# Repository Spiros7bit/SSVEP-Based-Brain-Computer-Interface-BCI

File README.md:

# SSVEP-Based Brain-Computer Interface

## Overview

This project implements a real-time Steady-State Visually Evoked Potential (SSVEP) Brain-Computer Interface (BCI) using an ESP32 microcontroller and a custom PCB for analog interface. It was developed as part of a thesis and demonstrates how EEG signals can be processed and classified in real time on embedded hardware.

The system detects brain responses to visual stimuli at specific frequencies and converts them into control decisions.

---

## System Architecture

The signal processing pipeline consists of the following stages:

1. **Analog Interface**
   
   * Instrumentation Amplifier
   * Low Pass Filter, Sallen Key, 2 order
   * AC amplifier
   * Notch 50 Hz filter
   * Final AC Amplifier
   * Right Leg Driver circuit
     
3. **Signal Acquisition**

   * ADC sampling at 1 kHz
   * Hardware timer interrupt for precise timing

4. **Preprocessing**

   * DC offset removal (IIR high-pass filter)
   * FIR band-pass filtering

5. **Feature Extraction**

   * Goertzel algorithm for frequency detection
   * Target frequencies: 10 Hz, 12 Hz, 20 Hz, 24 Hz

6. **Decision Making**

   * Argmax power comparison
   * Median Absolute Deviation (MAD)-based classifier

7. **Output**

   * Real-time signal visualization via Serial Plotter
   * Classification results (Argmax & MAD)

---

## Features

* Analog interface and Acquition System
* Real-time processing on ESP32
* 1 kHz sampling using hardware timer interrupts
* Efficient fixed-point DSP implementation
* FIR filtering with circular buffer
* Sliding window Goertzel analysis (with overlap)
* Robust classification using MAD
* Serial output for debugging and visualization

---

## Hardware Requirements

* ESP32 development board
* EEG acquisition circuit (as designed in the thesis)
* Electrodes and analog front-end

**ADC Input:** GPIO34 (ADC1_CHANNEL_6)

---

## Software Requirements

* Arduino IDE or PlatformIO
* ESP32 board support package

---

## How It Works

### Sampling

A hardware timer triggers ADC sampling at 1000 Hz. Each sample is processed in real time.

### DC Removal

A simple IIR filter removes the DC component from the signal:

```
dc_est = dc_est + k * (x - dc_est)
```

### FIR Filtering

A band-pass FIR filter is applied to isolate relevant EEG frequencies.

### Goertzel Algorithm

The Goertzel algorithm is used to compute the energy at specific target frequencies efficiently.

* Window size: 2048 samples
* Step size: 256 samples (overlap processing)

### Decision Logic

Two decision methods are implemented:

1. **Argmax**

   * Compares power between frequency groups

2. **MAD (Median Absolute Deviation)**

   * Computes a robust threshold based on signal statistics
   * Reduces noise and false detections

---

## Output Format

The system outputs data via Serial in the following format:

```
signal_value, argmax_decision, mad_decision
```

This can be visualized using the Arduino Serial Plotter.

---

## Project Structure

```
.
├── main.ino
├── fir_new_2_1000hz.h   # FIR filter coefficients
├── README.md
```

---

## Applications

* Brain-computer interfaces (BCI)
* Assistive technologies
* Neuroengineering research
* Real-time embedded DSP systems

---

## Future Improvements

* Add more target frequencies
* Improve classification accuracy
* Wireless data transmission (Bluetooth/WiFi)
* GUI for real-time monitoring
* Add a TinyML algorithm

---

## Author

Developed as part of a thesis project on SSVEP-based Brain-Computer Interfaces.

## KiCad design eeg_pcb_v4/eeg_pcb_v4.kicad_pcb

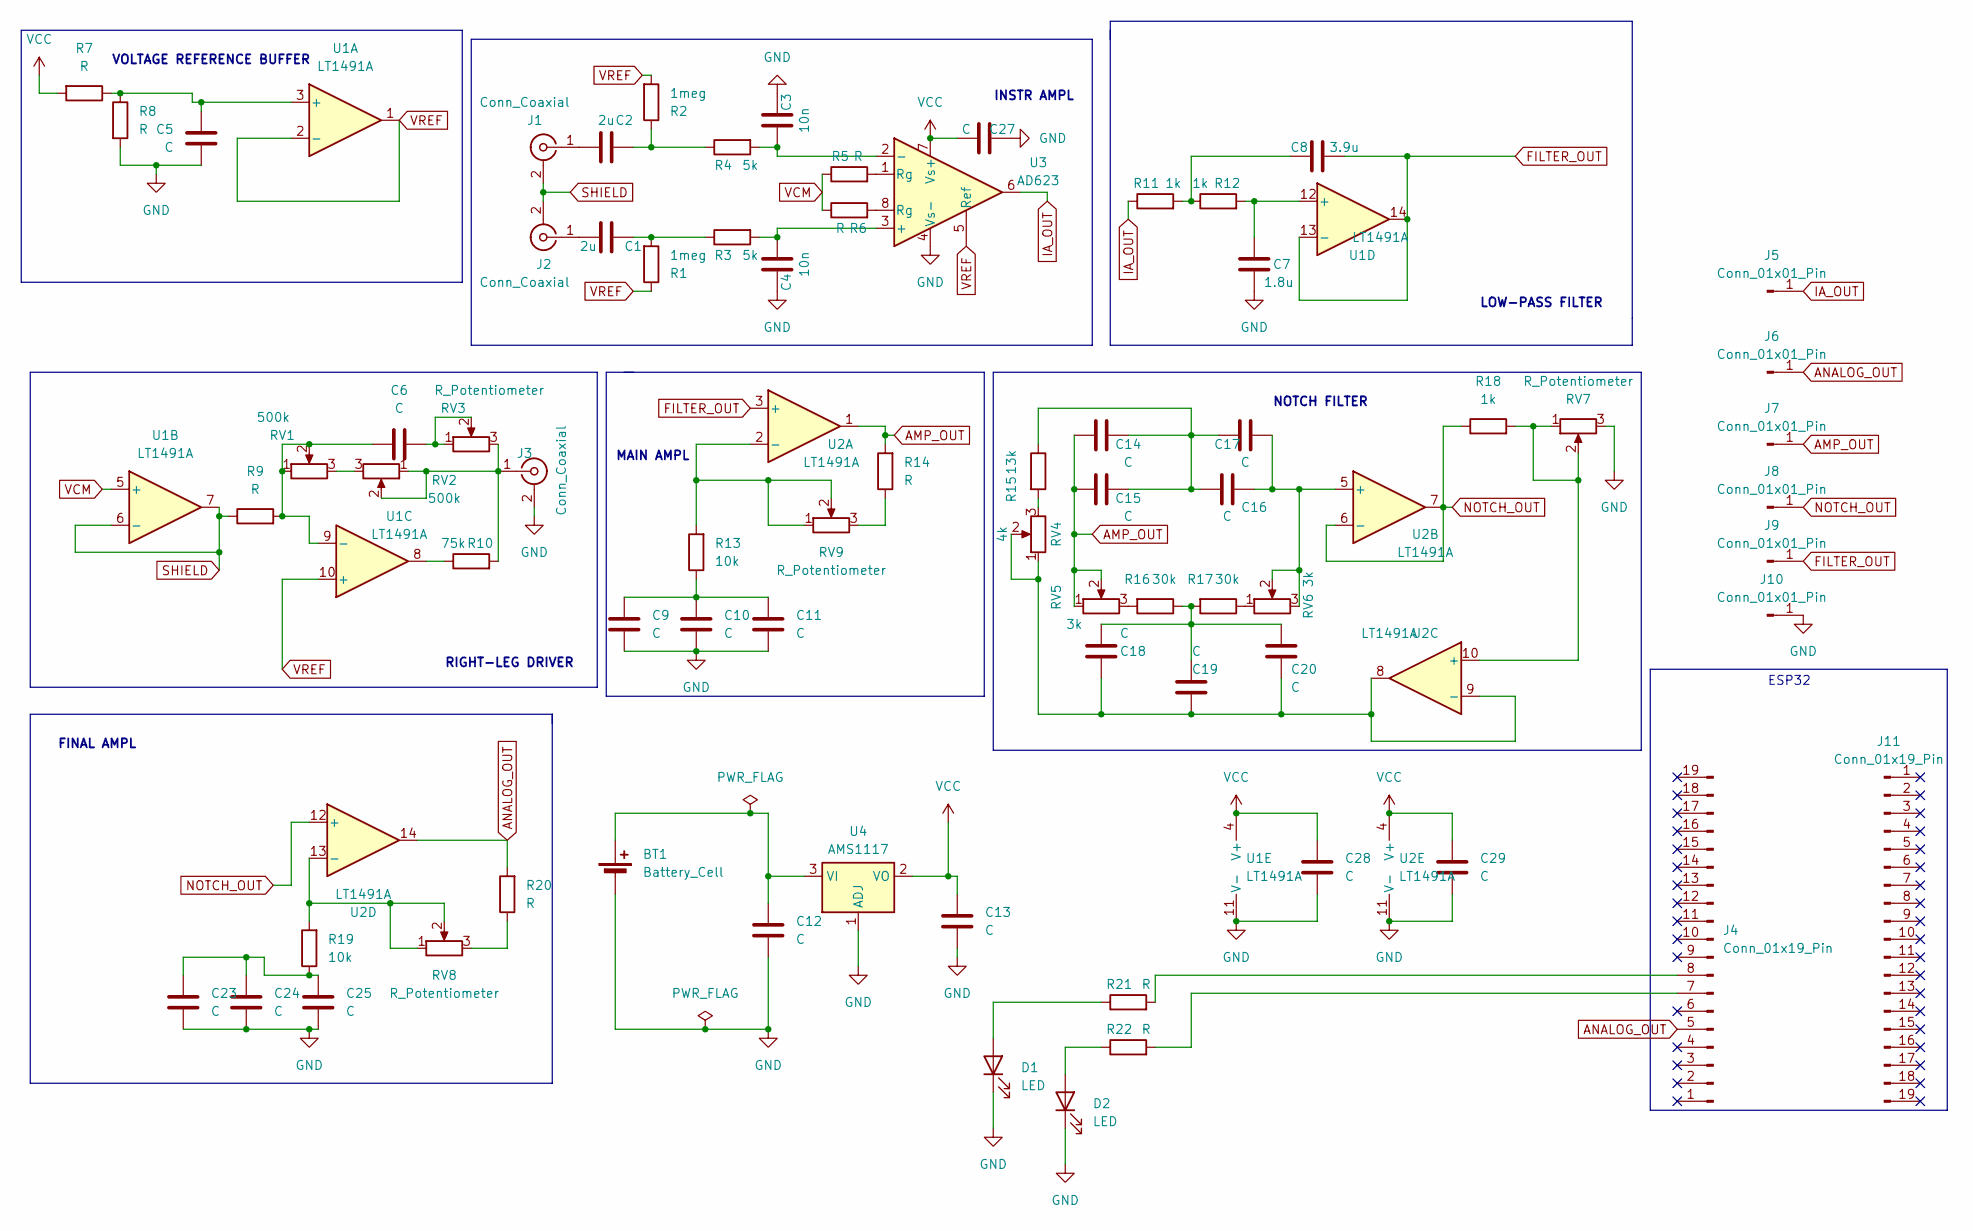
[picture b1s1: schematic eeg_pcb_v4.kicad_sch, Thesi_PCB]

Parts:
BT1: Battery_Cell; TerminalBlock_Altech_AK300-2_P5.00mm
C1, C2: 2u; C_1206_3216Metric
C3, C4: 10n; C_1206_3216Metric
C5, C6, C9, C10, C11, C12, C13, C14, C15, C16, C17, C18, C19, C20, C23, C24, C25, C27, C28, C29: C; C_1206_3216Metric
C7: 1.8u; C_1206_3216Metric
C8: 3.9u; C_1206_3216Metric
D1, D2: LED; LED_0805_2012Metric
J1, J2, J3: Conn_Coaxial; BNC_Amphenol_B6252HB-NPP3G-50_Horizontal
J4, J11: Conn_01x19_Pin; PinHeader_1x19_P2.54mm_Vertical
J5, J6, J7, J8, J9, J10: Conn_01x01_Pin; TestPoint_Pad_D1.0mm
R1, R2: 1meg; R_1206_3216Metric
R3, R4: 5k; R_1206_3216Metric
R5, R6, R7, R8, R9, R14, R20, R21, R22: R; R_1206_3216Metric
R10: 75k; R_1206_3216Metric
R11, R12, R18: 1k; R_1206_3216Metric
R13, R19: 10k; R_1206_3216Metric
R15: 13k; R_1206_3216Metric
R16, R17: 30k; R_1206_3216Metric
RV1, RV2: 500k; Potentiometer_Bourns_TC33X_Vertical
RV3, RV7, RV8, RV9: R_Potentiometer; Potentiometer_Bourns_TC33X_Vertical
RV4: 4k; Potentiometer_Bourns_TC33X_Vertical
RV5, RV6: 3k; Potentiometer_Bourns_TC33X_Vertical
U1, U2: LT1491A; SO-14_3.9x8.65mm_P1.27mm
U3: AD623; SO-8_3.9x4.9mm_P1.27mm
U4: AMS1117; SOT-223-3_TabPin2

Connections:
AMP_OUT: C14.1, C15.1, J7.1, R14.2, RV5.1, RV5.2, U2.1
ANALOG_OUT: J4.5, J6.1, R20.2, U2.14
FILTER_OUT: C8.2, J9.1, U1.13 (-), U1.14, U2.3 (+)
GND: BT1.2 (-), C3.1, C4.1, C5.2, C7.2, C9.2, C10.2, C11.2, C12.2, C13.2, C23.2, C24.2, C25.2, C27.2, C28.2, C29.2, D1.1 (K), D2.1 (K), J3.2 (Ext), J10.1, R8.2, RV7.3, U1.11 (V-), U2.11 (V-), U3.4 (Vs-), U4.1 (ADJ)
IA_OUT: J5.1, R11.1, U3.6
NOTCH_OUT: J8.1, R18.1, U2.6 (-), U2.7, U2.12 (+)
unnamed: BT1.1 (+), C12.1, U4.3 (VI)
unnamed: C1.2, R1.2, R3.1
unnamed: C2.2, R2.1, R4.1
unnamed: C6.2, RV3.1, RV3.2
unnamed: C8.1, R11.2, R12.1
unnamed: C9.1, C10.1, C11.1, R13.1
unnamed: C14.2, C15.2, C16.1, C17.1, R15.1
unnamed: C18.1, C19.1, C20.1, R16.1, R17.2
unnamed: C23.1, C24.1, C25.1, R19.1
unnamed: D1.2 (A), R21.1
unnamed: D2.2 (A), R22.1
unnamed: C2.1, J1.1 (In)
unnamed: C1.1, J2.1 (In)
unnamed: J3.1 (In), R10.2, RV2.1, RV2.2, RV3.3
unnamed: J4.7, R22.2
unnamed: J4.8, R21.2
unnamed: R5.2, U3.1 (Rg)
unnamed: R6.2, U3.8 (Rg)
unnamed: R10.1, U1.8
unnamed: R14.1, RV9.3
unnamed: R15.2, RV4.3
unnamed: R16.2, RV5.3
unnamed: R17.1, RV6.1
unnamed: R20.1, RV8.3
unnamed: RV1.3, RV2.3
unnamed: C5.1, R7.1, R8.1, U1.3 (+)
unnamed: C6.1, R9.2, RV1.1, RV1.2, U1.9 (-)
unnamed: C7.1, R12.2, U1.12 (+)
unnamed: R13.2, RV9.1, RV9.2, U2.2 (-)
unnamed: C16.2, C17.2, RV6.2, RV6.3, U2.5 (+)
unnamed: R18.2, RV7.1, RV7.2, U2.10 (+)
unnamed: C18.2, C19.2, C20.2, RV4.1, RV4.2, U2.8, U2.9 (-)
unnamed: R19.2, RV8.1, RV8.2, U2.13 (-)
unnamed: C4.2, R3.2, U3.3 (+)
unnamed: C3.2, R4.2, U3.2 (-)
SHIELD: J1.2 (Ext), J2.2 (Ext), R9.1, U1.6 (-), U1.7
VCC: C13.1, C27.1, C28.1, C29.1, R7.2, U1.4 (V+), U2.4 (V+), U3.7 (Vs+), U4.2 (VO)
VCM: R5.1, R6.1, U1.5 (+)
VREF: R1.1, R2.2, U1.1, U1.2 (-), U1.10 (+), U3.5 (Ref)

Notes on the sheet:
RIGHT-LEG DRIVER
LOW-PASS FILTER
NOTCH FILTER
ESP32
MAIN AMPL
INSTR AMPL
VOLTAGE REFERENCE BUFFER
FINAL AMPL

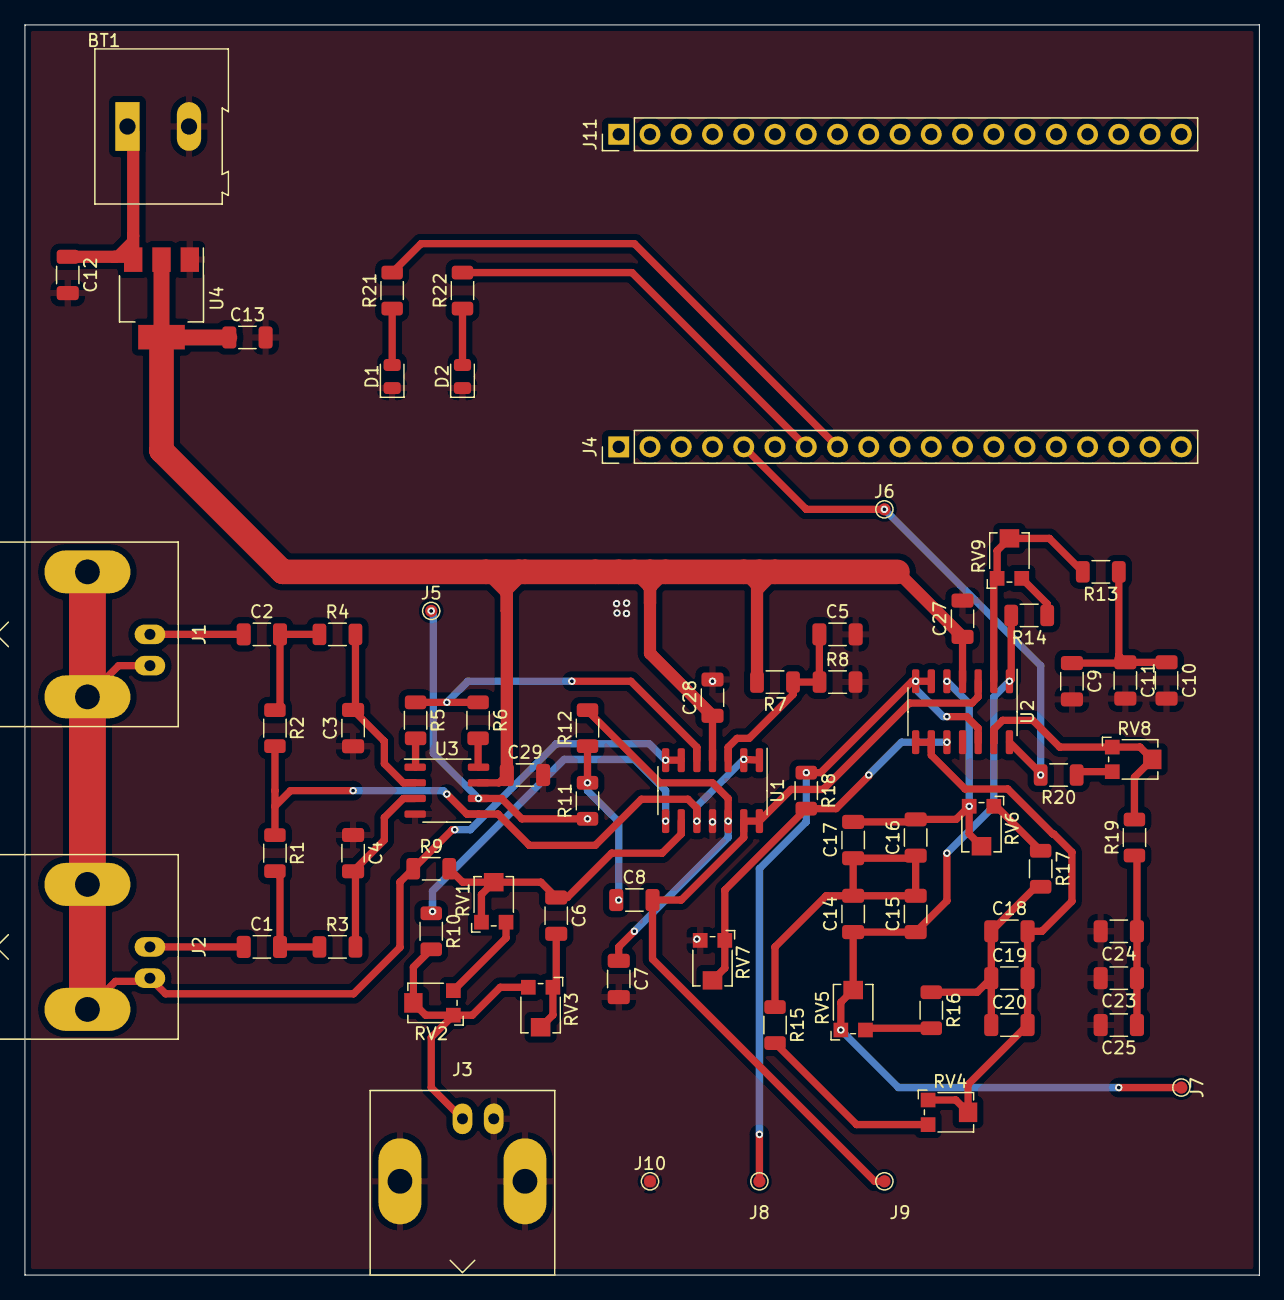
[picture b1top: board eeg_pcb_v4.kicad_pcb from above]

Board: 2 copper layers, 100.3 x 101.6 mm, 75 parts (0 on the bottom side), 45 nets.

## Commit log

2026-03-23 scr.ino, fir_new_2_1000hz.h
    First
2026-03-23 Create README.md
    add README
2026-04-29 Add files via upload
    Upload the pcb files
